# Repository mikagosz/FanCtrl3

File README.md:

## FanCtrl3

**A USB-powered controller for three 4-pin PWM fans, driven by the CPU temperature
of a Proxmox VE host.**

One USB cable to the host is all it needs — power, control and fan speed readings
all go over it. The fan curve runs **inside the controller**, so a host reboot, a
crashed service or a pulled cable never leaves the fans stopped.

Designed for small home servers and mini PCs running Proxmox: the machine sits in a
closed cabinet, its own fan is not enough for the cabinet, and a set of quiet 120 mm
fans should spin up only when the server actually works.

> [!NOTE]
> FanCtrl3 is a hobby project, built in spare time. Updates may not come often —
> but ideas, questions and build reports are always welcome (see
> [Contact and contributions](#contact-and-contributions)).

---

## Project status

> [!WARNING]
> **FanCtrl3 has not been tested on real hardware yet.** Hardware testing is coming
> soon; this section will be updated with the results. Until the first boards have
> run for a while, treat this as a reviewed design, not a proven product.

### Verified without hardware

| Area | How | Result |
|---|---|---|
| Schematics | KiCad ERC, both variants | 0 errors, 0 warnings |
| Pro PCB | KiCad DRC with schematic parity | 0 violations, 0 unconnected pads, 0 parity issues |
| Lite perfboard | the generator's own checker | every net connected, no hole shared by two nets, no wire through a foreign pad, no overlapping parts |
| Enclosure | intersection of the enclosure with the component bodies | 0 collisions, both variants |
| Control logic | 22 unit tests, run under CPython **and** MicroPython | all pass |
| Firmware `main.py` | runs under the MicroPython unix port on stubbed hardware: replies, 25 kHz inverted PWM, watchdog; `SERVICE` and service mode; `SAVE` success and failure (12 checks) | all pass |
| Host daemon and CLI | 10 unit tests (Intel and AMD sensors, several CPU packages, CLI errors, a silent socket client) and 13 end-to-end tests against a simulated controller: sensor selection, curve, `status`, `send`, `calibrate` (incl. a dead fan and failsafe), clean stop, restart without a temperature, crash → failsafe | all pass |

Every push and pull request runs these tests on GitHub Actions.

### Not tested yet

- Anything on a real board: soldering, the 12 V rail, the current limiter and its
  `FAULT` signal, real fan speeds from the tachometers, the DS18B20 probe, the LED,
  the watchdog, USB behaviour with and without a host.
- Power drawn from a real USB port with three fans at 100 %.
- The udev rule on a real Pico (`2e8a:0005` is MicroPython's default ID).
- Printing and fitting the enclosure; the Lite mounting-hole positions.

### Known issues

- AMD support (`k10temp`, `zenpower`) is tested only against simulated sensors so
  far — a report from a real AMD host is welcome.
- `tests/test_main_smoke.sh` depends on timing and can fail on a heavily loaded
  machine; run it again before looking for a bug.

## Features

- **Three 4-pin PWM fans**, 25 kHz PWM and tachometer reading on every channel.
- **Powered from USB only.** An on-board step-up makes the 12 V for the fans; a
  TI TPS2553 current-limited switch limits the fan side to 465–570 mA — the
  budget of a USB 2.0 port — and reports an overload to the controller.
- **Curve in the controller, temperature from the host.** A small daemon on the
  Proxmox host sends the CPU package temperature (Intel or AMD) every 5 seconds; the
  controller applies a curve with hysteresis and ramping.
- **Safe by default.** No temperature for 30 s → fans at 100 %. A dead
  microcontroller → the output transistors switch off → fans at 100 %. A clean host
  shutdown → fans rest at 20 % instead of alarming.
- **Ambient probe.** A DS18B20 on a cable measures the air in the cabinet and raises
  the fans on its own above 40 °C (60 %) and 45 °C (100 %).
- **Stall detection** per fan, per-fan minimum duty and a `calibrate` command that
  measures it.
- **Two variants, one firmware** — see below.
- **Host side needs nothing but Python 3's standard library**, a udev rule and a
  systemd unit.

## Two variants

| | **FanCtrl3 Lite** | **FanCtrl3 Pro** |
|---|---|---|
| Build | modules on a 72 × 47 mm perfboard (SCI PC-3) | custom 2-layer PCB, 90 × 60 mm |
| Soldering | through-hole only (plus one SOT-23-6 on an adapter) | 0805/1206 and SOT-23 by hand, no QFN |
| 12 V | Pololu U3V16F12 module | TI LM27313 boost on the board (12.4 V) |
| PWM output | BC547B, open collector | 2N7002, open drain |
| Current limit | TPS2553 on a SparkFun SOT-23 → DIP adapter | TPS2553 on the board |
| Pico | in sockets, removable | soldered flat |
| Build guide | [docs/build-lite.md](docs/build-lite.md) | [docs/build-pro.md](docs/build-pro.md) |

Both use the same pinout and run the same firmware.

<table>
  <tr>
    <td align="center"><br><sub>Lite — perfboard wiring drawing</sub></td>
    <td align="center"><br><sub>Pro — PCB, top</sub></td>
  </tr>
  <tr>
    <td align="center"><br><sub>Lite — enclosure</sub></td>
    <td align="center"><br><sub>Pro — enclosure</sub></td>
  </tr>
</table>

## How it works

```
 Proxmox host                                 FanCtrl3
┌────────────────────────┐   USB cable    ┌──────────────────────────────────────┐
│ CPU temp ─► fanctl     │  power + data  │ Pico: curve, hysteresis, failsafe    │
│             daemon ────┼───────────────►│  ├─ PWM ×3 ──► open collector/drain  │
│  TEMP 54.0 every 5 s   │◄───────────────│  ├─ tach ×3 ◄── fans                 │
│  STATUS, alarms        │                │  └─ DS18B20 ◄── ambient probe        │
└────────────────────────┘                │                                      │
                                          │ VBUS ─► TPS2553 ─► 12V boost ─► fans │
                                          │         (≈0.5 A)                     │
                                          └──────────────────────────────────────┘
```

The link is plain text over USB CDC — `TEMP 54.0`, `STATUS`, `SET 1 40` — so it can
be driven by hand from any terminal. Full protocol: [docs/firmware.md](docs/firmware.md).

## Power budget

The whole controller lives on one USB 2.0 port, which is allowed to supply
**500 mA**. The design is sized for three low-power 120 mm PWM fans rated at up
to **0.6 W each** (for example Noctua NF-P12 redux-1300 PWM):

3 × 0.6 W = 1.8 W at 12 V → ÷ 0.85 converter efficiency + ≈ 0.15 W for the Pico
≈ **0.45 A from the port**.

> [!CAUTION]
> Fans rated above 0.6 W each will not fit this budget. The TPS2553 limits the fan
> side to 465–570 mA and reports `FAULT`, but the fans will not reach full speed.
> Check the rated **input power** of your fans before you build.

## Getting started

1. **Pick a variant** and order the parts — [docs/bill-of-materials.md](docs/bill-of-materials.md).
2. **Build the board** — [Lite](docs/build-lite.md) or [Pro](docs/build-pro.md).
3. **Print the enclosure** — [docs/enclosure.md](docs/enclosure.md).
4. **Flash the firmware** — [docs/firmware.md](docs/firmware.md):
   MicroPython for `RPI_PICO`, then `firmware/flash.sh`.
5. **Install the host side on Proxmox** — [docs/host-proxmox.md](docs/host-proxmox.md):
   ```bash
   sh host/install.sh        # as root on the Proxmox host
   fanctl status
   fanctl calibrate          # finds the lowest duty each fan still spins at
   ```

## Repository layout

| Path | What is inside |
|---|---|
| [`hardware/tools/`](hardware/tools/) | generators — the design lives in code: [`design_pro.py`](hardware/tools/design_pro.py) and [`design_lite.py`](hardware/tools/design_lite.py) are the single source of truth |
| [`hardware/pro/`](hardware/pro/) | KiCad project of the Pro PCB, schematic PDF, [`fabrication/`](hardware/pro/fabrication/) Gerbers + drill ZIP and BOM, [`preview/`](hardware/pro/preview/) 3D renders |
| [`hardware/lite/`](hardware/lite/) | Lite schematic (KiCad + PDF), perfboard drawing (SVG) and wiring table |
| [`hardware/enclosure/`](hardware/enclosure/) | parametric OpenSCAD enclosure and ready STL files for both variants |
| [`firmware/`](firmware/) | MicroPython for the Pico: [`logic.py`](firmware/logic.py) (no hardware, testable) and [`main.py`](firmware/main.py) (pins) |
| [`host/`](host/) | `fanctl` daemon and CLI, udev rule, systemd unit, installer |
| [`sim/`](sim/) | the controller on a pseudo-terminal, for testing the host side without hardware |
| [`tests/`](tests/) | everything that runs without hardware: [`tests/run_all.sh`](tests/run_all.sh) |
| [`docs/`](docs/) | documentation |

## Documentation

- [Hardware design](docs/hardware.md) — circuit description, pinout, design decisions
- [Bill of materials](docs/bill-of-materials.md) — both variants, with suggested shop links
- [Building FanCtrl3 Lite](docs/build-lite.md) — perfboard assembly
- [Building FanCtrl3 Pro](docs/build-pro.md) — ordering the PCB and hand soldering
- [Enclosure](docs/enclosure.md) — printing and assembly
- [Firmware](docs/firmware.md) — flashing, control behaviour, serial protocol
- [Host software on Proxmox](docs/host-proxmox.md) — installation and `fanctl`
- [Development](docs/development.md) — regenerating the outputs, running the tests

## Contact and contributions

Ideas, improvements, a better circuit, a build report or a question — all welcome.
Open an issue on this repository or write to **support@fractal8.eu**. See
[CONTRIBUTING.md](CONTRIBUTING.md).

## Support the project

FanCtrl3 is built in spare time. If it is useful to you, you can support its
development through **[GitHub Sponsors](https://github.com/sponsors/mikagosz)** —
it helps pay for parts and prototype boards.

## Licence

MIT — see [LICENSE](LICENSE). This covers the hardware design files, the firmware
and the host software.

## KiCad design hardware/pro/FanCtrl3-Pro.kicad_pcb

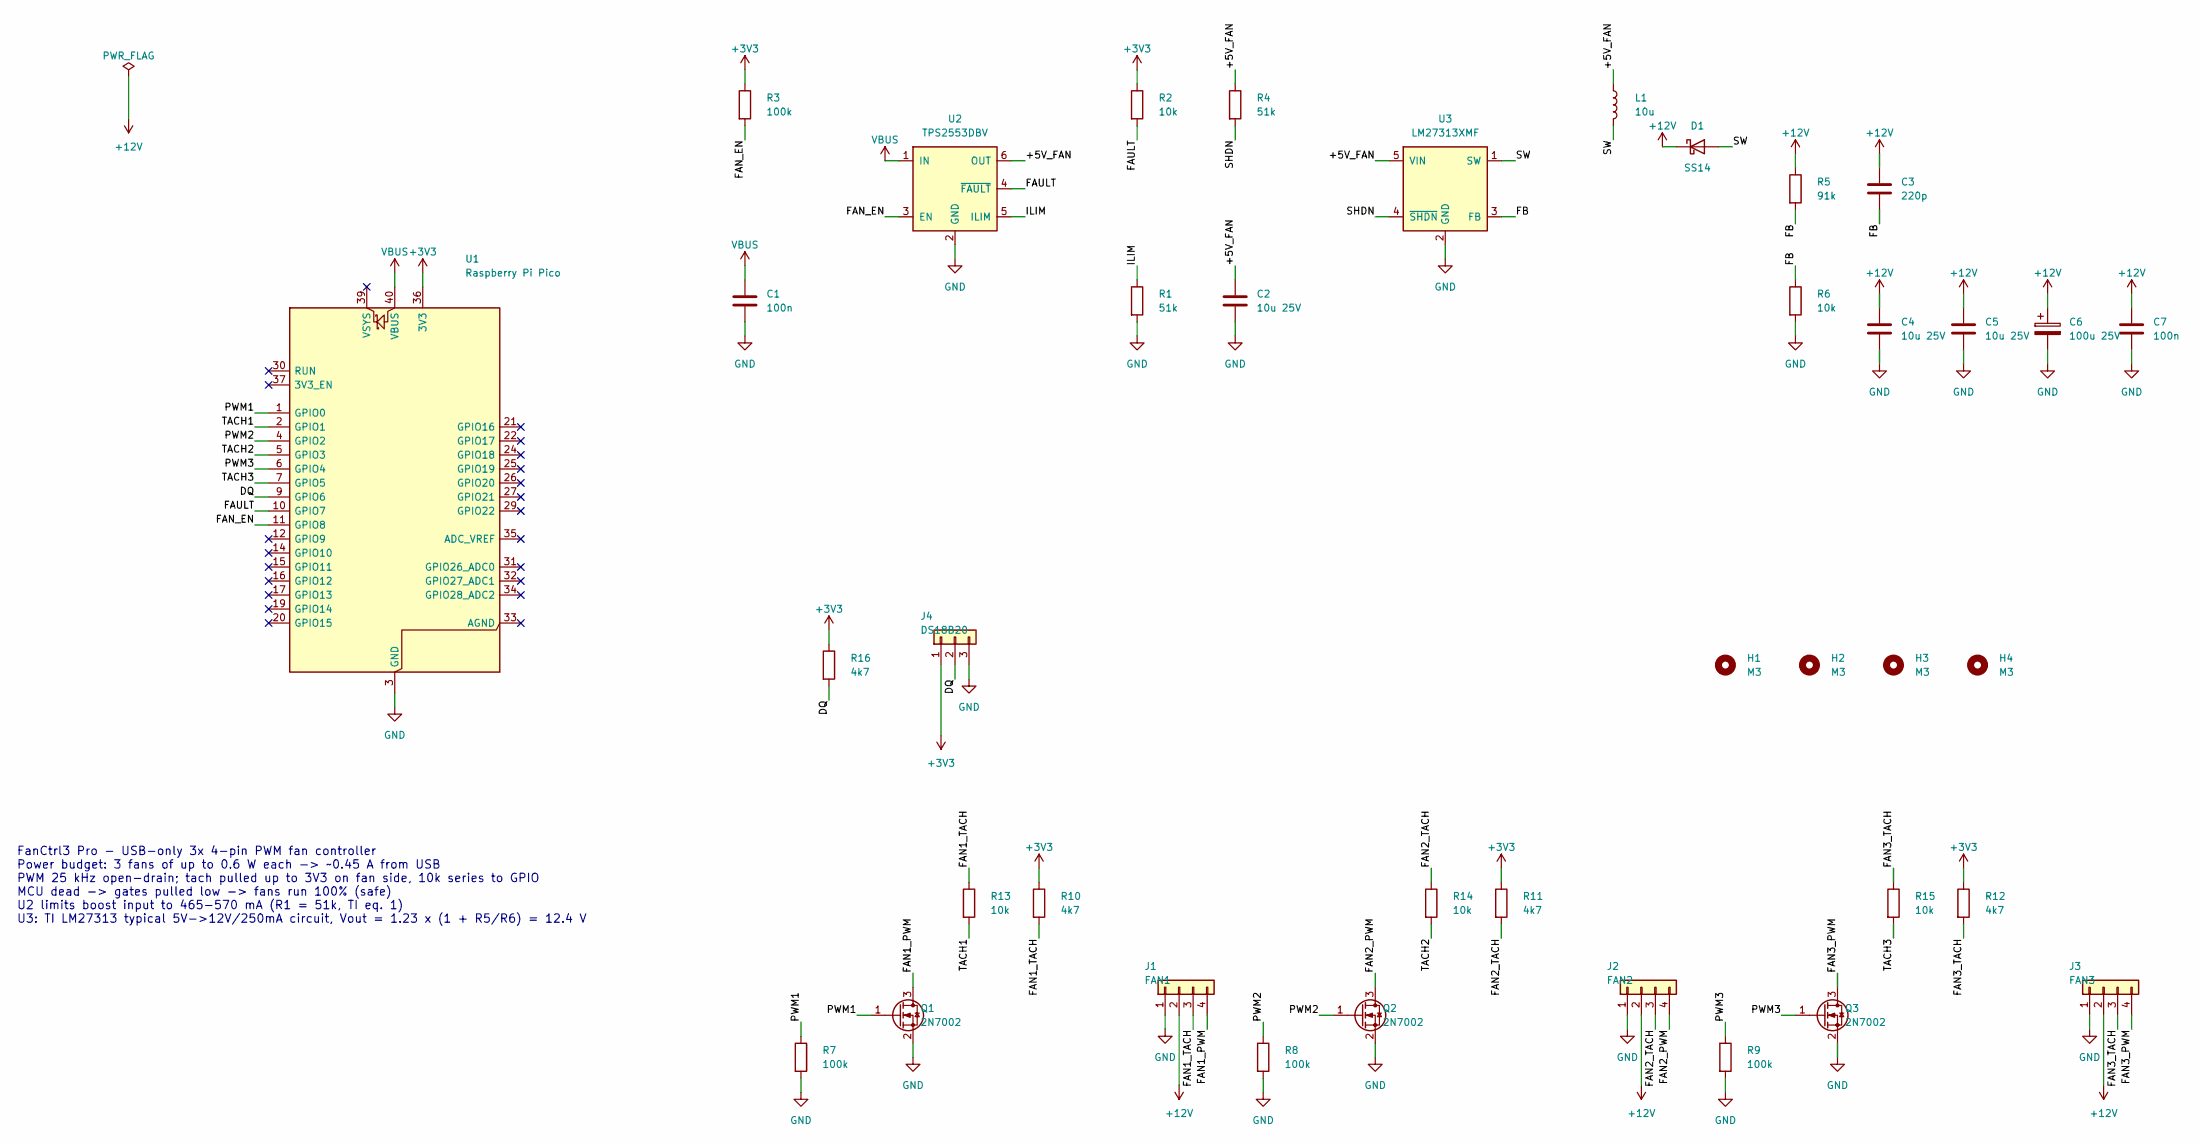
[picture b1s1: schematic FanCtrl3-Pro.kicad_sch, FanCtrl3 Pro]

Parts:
C1, C7: 100n; C_0805_2012Metric_Pad1.18x1.45mm_HandSolder
C2, C4, C5: 10u 25V; C_1206_3216Metric_Pad1.33x1.80mm_HandSolder
C3: 220p; C_0805_2012Metric_Pad1.18x1.45mm_HandSolder
C6: 100u 25V; CP_Radial_D6.3mm_P2.50mm
D1: SS14; D_SMA_Handsoldering
H1, H2, H3, H4: M3; MountingHole_3.2mm_M3
J1: FAN1; Molex_KK-254_AE-6410-04A_1x04_P2.54mm_Vertical
J2: FAN2; Molex_KK-254_AE-6410-04A_1x04_P2.54mm_Vertical
J3: FAN3; Molex_KK-254_AE-6410-04A_1x04_P2.54mm_Vertical
J4: DS18B20; TerminalBlock_Xinya_XY308-2.54-3P_1x03_P2.54mm_Horizontal
L1: 10u; L_Changjiang_FNR5040S
Q1, Q2, Q3: 2N7002; SOT-23_Handsoldering
R1, R4: 51k; R_0805_2012Metric_Pad1.20x1.40mm_HandSolder
R2, R6, R13, R14, R15: 10k; R_0805_2012Metric_Pad1.20x1.40mm_HandSolder
R3, R7, R8, R9: 100k; R_0805_2012Metric_Pad1.20x1.40mm_HandSolder
R5: 91k; R_0805_2012Metric_Pad1.20x1.40mm_HandSolder
R10, R11, R12, R16: 4k7; R_0805_2012Metric_Pad1.20x1.40mm_HandSolder
U1: Raspberry Pi Pico; RaspberryPi_Pico_SMD_HandSolder
U2: TPS2553DBV; SOT-23-6_Handsoldering
U3: LM27313XMF; SOT-23-5_HandSoldering

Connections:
+3V3: J4.1, R2.1, R3.1, R10.1, R11.1, R12.1, R16.1, U1.36 (3V3)
+12V: C3.1, C4.1, C5.1, C6.1, C7.1, D1.1 (K), J1.2, J2.2, J3.2, R5.1
/+5V_FAN: C2.1, L1.1, R4.1, U2.6 (OUT), U3.5 (VIN)
/DQ: J4.2, R16.2, U1.9 (GPIO6)
/FAN1_PWM: J1.4, Q1.3 (D)
/FAN1_TACH: J1.3, R10.2, R13.1
/FAN2_PWM: J2.4, Q2.3 (D)
/FAN2_TACH: J2.3, R11.2, R14.1
/FAN3_PWM: J3.4, Q3.3 (D)
/FAN3_TACH: J3.3, R12.2, R15.1
/FAN_EN: R3.2, U1.11 (GPIO8), U2.3 (EN)
/FAULT: R2.2, U1.10 (GPIO7), U2.4 (~FAULT)
/FB: C3.2, R5.2, R6.1, U3.3 (FB)
/ILIM: R1.1, U2.5 (ILIM)
/PWM1: Q1.1 (G), R7.1, U1.1 (GPIO0)
/PWM2: Q2.1 (G), R8.1, U1.4 (GPIO2)
/PWM3: Q3.1 (G), R9.1, U1.6 (GPIO4)
/SHDN: R4.2, U3.4 (~SHDN)
/SW: D1.2 (A), L1.2, U3.1 (SW)
/TACH1: R13.2, U1.2 (GPIO1)
/TACH2: R14.2, U1.5 (GPIO3)
/TACH3: R15.2, U1.7 (GPIO5)
GND: C1.2, C2.2, C4.2, C5.2, C6.2, C7.2, J1.1, J2.1, J3.1, J4.3, Q1.2 (S), Q2.2 (S), Q3.2 (S), R1.2, R6.2, R7.2, R8.2, R9.2, U1.3 (GND), U1.8 (GND), U1.13 (GND), U1.18 (GND), U1.23 (GND), U1.28 (GND), U1.38 (GND), U2.2 (GND), U3.2 (GND)
VBUS: C1.1, U1.40 (VBUS), U2.1 (IN)

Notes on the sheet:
FanCtrl3 Pro - USB-only 3x 4-pin PWM fan controller Power budget: 3 fans of up to 0.6 W each -> ~0.45 A from USB PWM 25 kHz open-drain; tach pulled up to 3V3 on fan side, 10k series to GPIO MCU dead -> gates pulled low -> fans run 100% (safe) U2 limits boost input to 465-570 mA (R1 = 51k, TI eq. 1)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

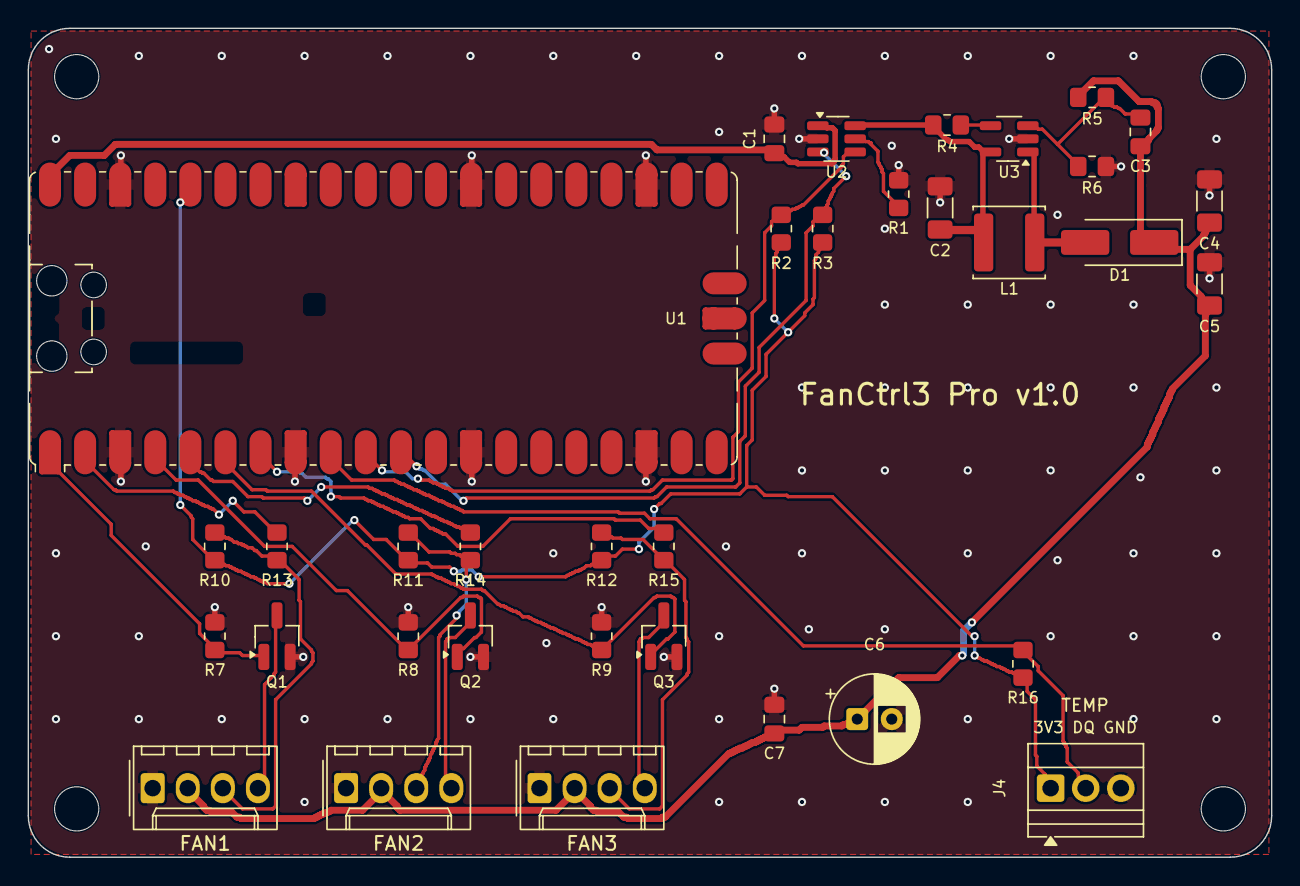
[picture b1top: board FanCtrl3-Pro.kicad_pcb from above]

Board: 2 copper layers, 90.0 x 60.0 mm, 39 parts (0 on the bottom side), 24 nets.

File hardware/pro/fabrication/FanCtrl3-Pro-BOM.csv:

"References","Value","Footprint","TME","Qty","Note"
"C1,C7","100n","Capacitor_SMD:C_0805_2012Metric_Pad1.18x1.45mm_HandSolder","0805B104K500CT","2",""
"C2,C4,C5","10u 25V","Capacitor_SMD:C_1206_3216Metric_Pad1.33x1.80mm_HandSolder","TMK316AB7106KLHT","3",""
"C3","220p","Capacitor_SMD:C_0805_2012Metric_Pad1.18x1.45mm_HandSolder","0805N221J500CT","1","feed-forward, fz ~ 8 kHz"
"C6","100u 25V","Capacitor_THT:CP_Radial_D6.3mm_P2.50mm","CE-100/25PHT-Y","1",""
"D1","SS14","Diode_SMD:D_SMA_Handsoldering","SS14-FAI","1",""
"J1,J2,J3","FAN1,FAN2,FAN3","Connector_Molex:Molex_KK-254_AE-6410-04A_1x04_P2.54mm_Vertical","MX-47053-1000","3",""
"J4","DS18B20","TerminalBlock:TerminalBlock_Xinya_XY308-2.54-3P_1x03_P2.54mm_Horizontal","DG308-2.54-03P","1","probe: red VDD, yellow DQ, black GND"
"L1","10u","Inductor_SMD:L_Changjiang_FNR5040S","DJNR5040-100-S","1",""
"Q1,Q2,Q3","2N7002","Package_TO_SOT_SMD:SOT-23_Handsoldering","2N7002-DIO","3",""
"R1,R4","51k","Resistor_SMD:R_0805_2012Metric_Pad1.20x1.40mm_HandSolder","SMD0805-51K-1%","2","current limit 465-570 mA"
"R2,R6,R13,R14,R15","10k","Resistor_SMD:R_0805_2012Metric_Pad1.20x1.40mm_HandSolder","SMD0805-10K-1%","5","limits current if fan tach is pulled up to 12 V"
"R3,R7,R8,R9","100k","Resistor_SMD:R_0805_2012Metric_Pad1.20x1.40mm_HandSolder","SMD0805-100K-1%","4","MCU dead -> MOSFET off -> fan 100%,fans powered by default"
"R5","91k","Resistor_SMD:R_0805_2012Metric_Pad1.20x1.40mm_HandSolder","SMD0805-91K-1%","1","Vout = 1.23 * (1 + 91/10) = 12.4 V"
"R10,R11,R12,R16","4k7","Resistor_SMD:R_0805_2012Metric_Pad1.20x1.40mm_HandSolder","SMD0805-4K7-1%","4","pull-up on fan side"
"U1","Raspberry Pi Pico","Module:RaspberryPi_Pico_SMD_HandSolder","SC0915","1",""
"U2","TPS2553DBV","Package_TO_SOT_SMD:SOT-23-6_Handsoldering","TPS2553DBVR","1",""
"U3","LM27313XMF","Package_TO_SOT_SMD:SOT-23-5_HandSoldering","LM27313XMF/NOPB","1",""

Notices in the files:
README.md:
License: MIT
